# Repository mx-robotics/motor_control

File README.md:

moved to https://github.com/mx-car/motor_shield_teensy3.2

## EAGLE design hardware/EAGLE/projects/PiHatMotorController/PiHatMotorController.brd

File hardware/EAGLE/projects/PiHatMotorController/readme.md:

# Pin Maps for 2M Inverter Board and Teensy

## 1M Board

*  SPI: There are 2 AMS Rotary Encoders that send info, so there are 2 CS Pins.
	* CS1: 9
  * CS2: 15/A1
	* CLK: 13
	* MOSI: 11
	* MISO: 12
  
* Current Sense
	* IS_W: A17
	* IS_V: A16
	* IS_U: A15
  * IS_W1: A12
	* IS_V2: A13
	* IS_U2: A17
  
* INHIBIT Pins 
	* INH_W: 33
	* INH_V: 3
	* INH_U: 24
  * INH_W2: 0
	* INH_V2: 1
	* INH_U2: 2
  
* Servo Pins:
	* S_PWM1: 32
	* S_PWM2: 25
  
* IN Pins (for actively controlling the half-bridges with PWM)
	* They do not directly connect to Teensy and must be connected with cables. Candidate pins that use FTM0 are adjacent and are **21, 22 and 23**.
	* IN_W: 10
	* IN_V: 6
	* IN_U: 5
  * IN_W2: 23
	* IN_V2: 22
	* IN_U2: 21
  
* Hall Pins
	* HALL_W: A13
	* HALL_U: A12
	* HALL_V: A11
  * HALL_W: A13
	* HALL_U: A12
	* HALL_V: A11

* I2C Pins 0
	* SDA0: 18
	* SCL0: 19
* I2C Pins 1:
	* SDA1: 30
	* SCL1: 29

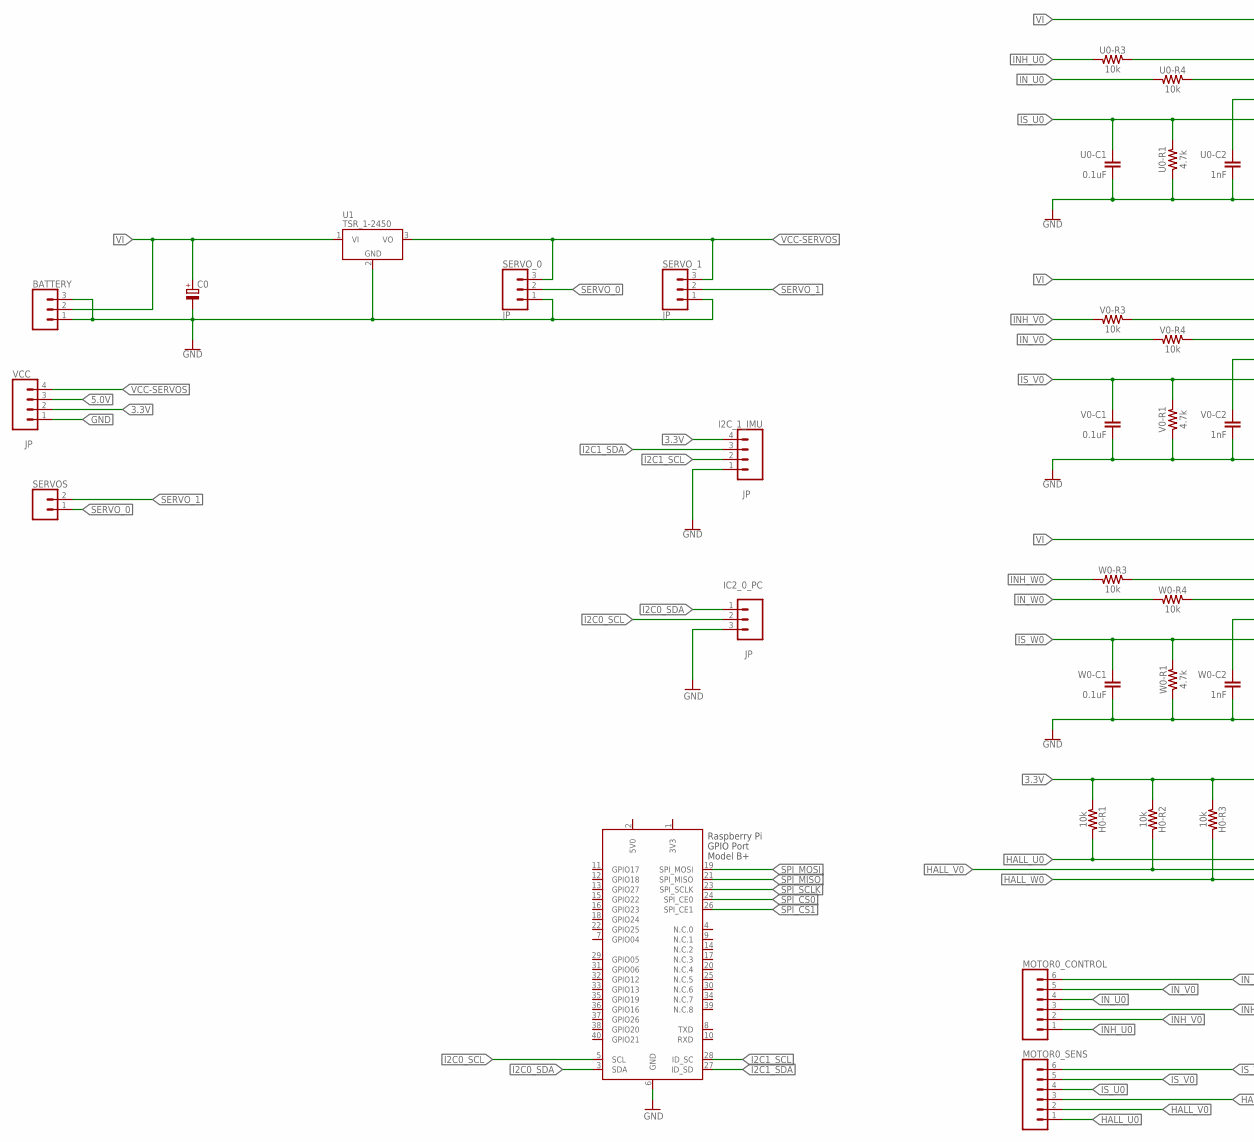
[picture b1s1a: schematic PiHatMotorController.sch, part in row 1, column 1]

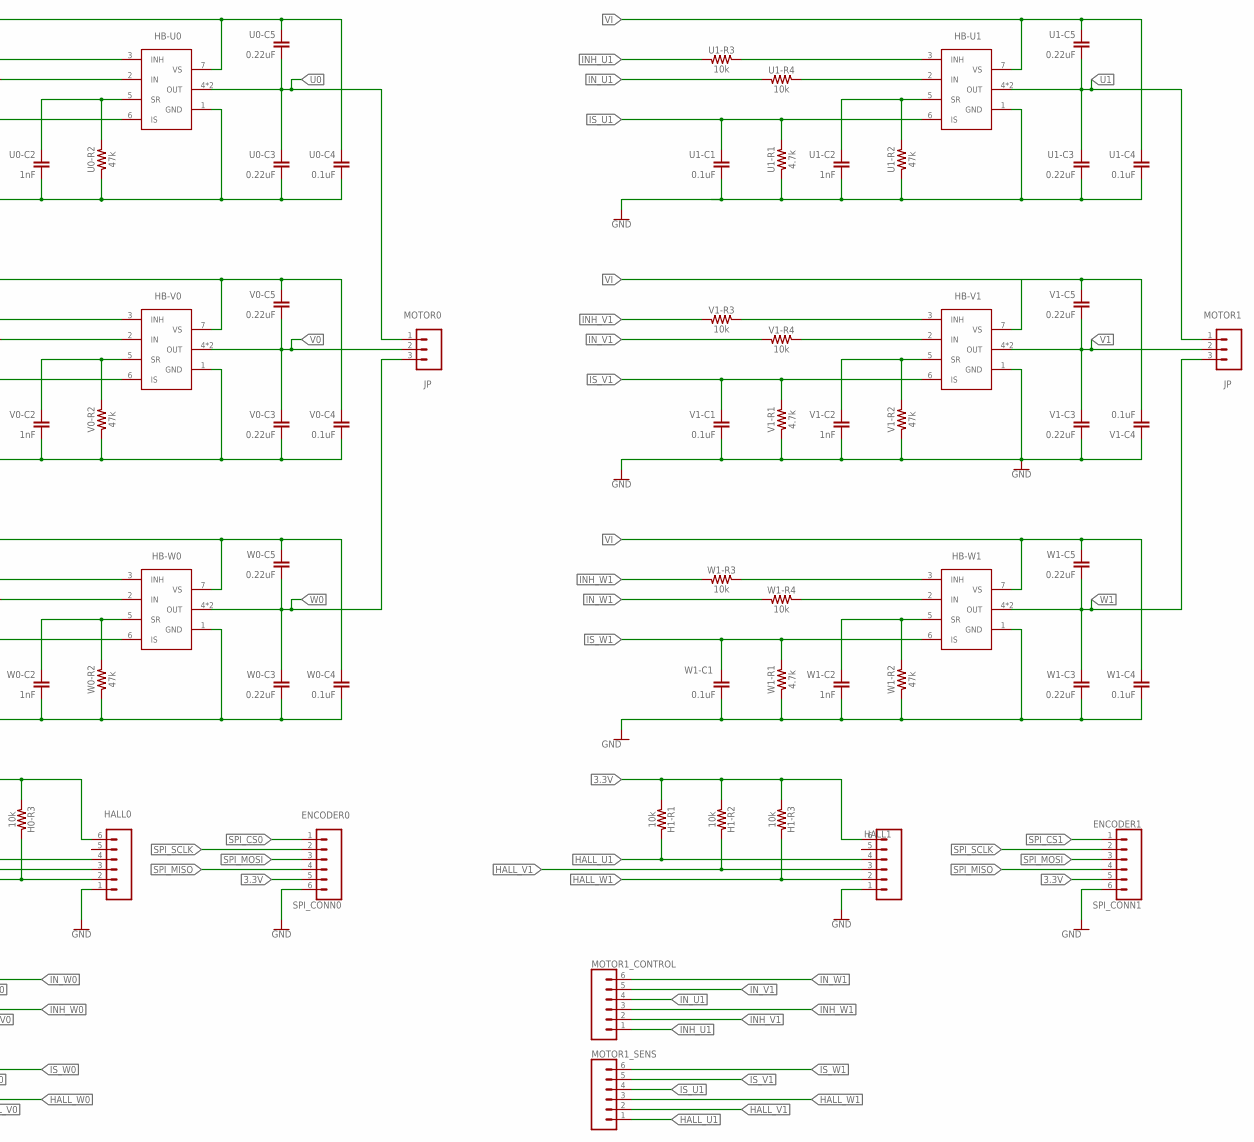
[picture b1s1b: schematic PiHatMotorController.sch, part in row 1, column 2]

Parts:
BATTERY: CONN_031X03_NO_SILK; 1X03_NO_SILK
C0: CPOL-EUE2,5-6E; E2,5-6E
H0-R1, H0-R2, H0-R3, H1-R1, H1-R2, H1-R3: 10k; 0603
HALL0, HALL1: CONN_06SMD-1MM; 1X06-1MM
HB-U0, HB-U1: IFX007TZZZZ; P-TO263-7-1
HB-V0, HB-V1: IFX007TZZZZ; P-TO263-7-1
HB-W0, HB-W1: IFX007TZZZZ; P-TO263-7-1
I2C_1_IMU: JP; 1X04_NO_SILK
IC2_0_PC: JP; 1X03_NO_SILK
MOTOR0, MOTOR1: JP; 1X03_NO_SILK
MOTOR0_CONTROL, MOTOR0_SENS, MOTOR1_CONTROL, MOTOR1_SENS: CONN_06NO_SILK_NO_POP; 1X06_NO_SILK
SERVOS: CONN_021X02_NO_SILK; 1X02_NO_SILK
SERVO_0, SERVO_1: JP; 1X03_NO_SILK
SPI_CONN0: ENCODER0; 1X06-1MM
SPI_CONN1: ENCODER1; 1X06-1MM
U0-C1, U0-C4, U1-C1, U1-C4: 0.1uF; 0603
U0-C2, U1-C2: 1nF; 0603
U0-C3, U0-C5, U1-C3, U1-C5: 0.22uF; 0603
U0-R1, U1-R1: 4.7k; 0603
U0-R2, U1-R2: 47k; 0603
U0-R3, U0-R4, U1-R3, U1-R4: 10k; 0603
U1: TSR_1-2450; TSR-1
V0-C1, V0-C4, V1-C1, V1-C4: 0.1uF; 0603
V0-C2, V1-C2: 1nF; 0603
V0-C3, V0-C5, V1-C3, V1-C5: 0.22uF; 0603
V0-R1, V1-R1: 4.7k; 0603
V0-R2, V1-R2: 47k; 0603
V0-R3, V0-R4, V1-R3, V1-R4: 10k; 0603
VCC: JP; 1X04_NO_SILK
W0-C1, W0-C4, W1-C1, W1-C4: 0.1uF; 0603
W0-C2, W1-C2: 1nF; 0603
W0-C3, W0-C5, W1-C3, W1-C5: 0.22uF; 0603
W0-R1, W1-R1: 4.7k; 0603
W0-R2, W1-R2: 47k; 0603
W0-R3, W0-R4, W1-R3, W1-R4: 10k; 0603
X1: RASPI_BOARD_B+_H; RASPI_BOARD_B+HAT

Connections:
3.3V: H0-R1.2, H0-R2.2, H0-R3.2, H1-R1.2, H1-R2.2, H1-R3.2, HALL0.6, HALL1.6, I2C_1_IMU.4, SPI_CONN0.5, SPI_CONN1.5, VCC.2
3V3: X1.1 (3V3)
5.0V: VCC.3
5V0: X1.2 (5V0)
GND: BATTERY.1, BATTERY.3, C0.-, HALL0.1, HALL1.1, HB-U0.1 (GND), HB-U1.1 (GND), HB-V0.1 (GND), HB-V1.1 (GND), HB-W0.1 (GND), HB-W1.1 (GND), I2C_1_IMU.1, IC2_0_PC.3, SERVO_0.1, SERVO_1.1, SPI_CONN0.6, SPI_CONN1.6, U0-C1.1, U0-C2.1, U0-C3.1, U0-C4.1, U0-R1.1, U0-R2.1, U1.2 (GND), U1-C1.1, U1-C2.1, U1-C3.1, U1-C4.1, U1-R1.1, U1-R2.1, V0-C1.1, V0-C2.1, V0-C3.1, V0-C4.1, V0-R1.1, V0-R2.1, V1-C1.1, V1-C2.1, V1-C3.1, V1-C4.1, V1-R1.1, V1-R2.1, VCC.1, W0-C1.1, W0-C2.1, W0-C3.1, W0-C4.1, W0-R1.1, W0-R2.1, W1-C1.1, W1-C2.1, W1-C3.1, W1-C4.1, W1-R1.1, W1-R2.1, X1.6 (GND)
HALL_U0: H0-R1.1, HALL0.4, MOTOR0_SENS.1
HALL_U1: H1-R1.1, HALL1.4, MOTOR1_SENS.1
HALL_V0: H0-R2.1, HALL0.3, MOTOR0_SENS.2
HALL_V1: H1-R2.1, HALL1.3, MOTOR1_SENS.2
HALL_W0: H0-R3.1, HALL0.2, MOTOR0_SENS.3
HALL_W1: H1-R3.1, HALL1.2, MOTOR1_SENS.3
HB_INH_U0: HB-U0.3 (INH), U0-R3.1
HB_INH_U1: HB-U1.3 (INH), U1-R3.1
HB_INH_V0: HB-V0.3 (INH), V0-R3.1
HB_INH_V1: HB-V1.3 (INH), V1-R3.1
HB_INH_W0: HB-W0.3 (INH), W0-R3.1
HB_INH_W1: HB-W1.3 (INH), W1-R3.1
HB_IN_U0: HB-U0.2 (IN), U0-R4.1
HB_IN_U1: HB-U1.2 (IN), U1-R4.1
HB_IN_V0: HB-V0.2 (IN), V0-R4.1
HB_IN_V1: HB-V1.2 (IN), V1-R4.1
HB_IN_W0: HB-W0.2 (IN), W0-R4.1
HB_IN_W1: HB-W1.2 (IN), W1-R4.1
I2C0_SCL: IC2_0_PC.2, X1.5 (SCL)
I2C0_SDA: IC2_0_PC.1, X1.3 (SDA)
I2C1_SCL: I2C_1_IMU.2, X1.28 (ID_SC)
I2C1_SDA: I2C_1_IMU.3, X1.27 (ID_SD)
INH_U0: MOTOR0_CONTROL.1, U0-R3.2
INH_U1: MOTOR1_CONTROL.1, U1-R3.2
INH_V0: MOTOR0_CONTROL.2, V0-R3.2
INH_V1: MOTOR1_CONTROL.2, V1-R3.2
INH_W0: MOTOR0_CONTROL.3, W0-R3.2
INH_W1: MOTOR1_CONTROL.3, W1-R3.2
IN_U0: MOTOR0_CONTROL.4, U0-R4.2
IN_U1: MOTOR1_CONTROL.4, U1-R4.2
IN_V0: MOTOR0_CONTROL.5, V0-R4.2
IN_V1: MOTOR1_CONTROL.5, V1-R4.2
IN_W0: MOTOR0_CONTROL.6, W0-R4.2
IN_W1: MOTOR1_CONTROL.6, W1-R4.2
IS_U0: HB-U0.6 (IS), MOTOR0_SENS.4, U0-C1.2, U0-R1.2
IS_U1: HB-U1.6 (IS), MOTOR1_SENS.4, U1-C1.2, U1-R1.2
IS_V0: HB-V0.6 (IS), MOTOR0_SENS.5, V0-C1.2, V0-R1.2
IS_V1: HB-V1.6 (IS), MOTOR1_SENS.5, V1-C1.2, V1-R1.2
IS_W0: HB-W0.6 (IS), MOTOR0_SENS.6, W0-C1.2, W0-R1.2
IS_W1: HB-W1.6 (IS), MOTOR1_SENS.6, W1-C1.2, W1-R1.2
SERVO_0: SERVOS.1, SERVO_0.2
SERVO_1: SERVOS.2, SERVO_1.2
SPI_CS0: SPI_CONN0.1, X1.24 (SPI_CE0)
SPI_CS1: SPI_CONN1.1, X1.26 (SPI_CE1)
SPI_MISO: SPI_CONN0.4, SPI_CONN1.4, X1.21 (SPI_MISO)
SPI_MOSI: SPI_CONN0.3, SPI_CONN1.3, X1.19 (SPI_MOSI)
SPI_SCLK: SPI_CONN0.2, SPI_CONN1.2, X1.23 (SPI_SCLK)
SR_U0: HB-U0.5 (SR), U0-C2.2, U0-R2.2
SR_U1: HB-U1.5 (SR), U1-C2.2, U1-R2.2
SR_V0: HB-V0.5 (SR), V0-C2.2, V0-R2.2
SR_V1: HB-V1.5 (SR), V1-C2.2, V1-R2.2
SR_W0: HB-W0.5 (SR), W0-C2.2, W0-R2.2
SR_W1: HB-W1.5 (SR), W1-C2.2, W1-R2.2
U0: HB-U0.4 (OUT), HB-U0.8 (OUT), MOTOR0.1, U0-C3.2, U0-C5.2
U1: HB-U1.4 (OUT), HB-U1.8 (OUT), MOTOR1.1, U1-C3.2, U1-C5.2
V0: HB-V0.4 (OUT), HB-V0.8 (OUT), MOTOR0.2, V0-C3.2, V0-C5.2
V1: HB-V1.4 (OUT), HB-V1.8 (OUT), MOTOR1.2, V1-C3.2, V1-C5.2
VCC-SERVOS: SERVO_0.3, SERVO_1.3, U1.3 (VO), VCC.4
VI: BATTERY.2, C0.+, HB-U0.7 (VS), HB-U1.7 (VS), HB-V0.7 (VS), HB-V1.7 (VS), HB-W0.7 (VS), HB-W1.7 (VS), U0-C4.2, U0-C5.1, U1.1 (VI), U1-C4.2, U1-C5.1, V0-C4.2, V0-C5.1, V1-C4.2, V1-C5.1, W0-C4.2, W0-C5.1, W1-C4.2, W1-C5.1
W0: HB-W0.4 (OUT), HB-W0.8 (OUT), MOTOR0.3, W0-C3.2, W0-C5.2
W1: HB-W1.4 (OUT), HB-W1.8 (OUT), MOTOR1.3, W1-C3.2, W1-C5.2

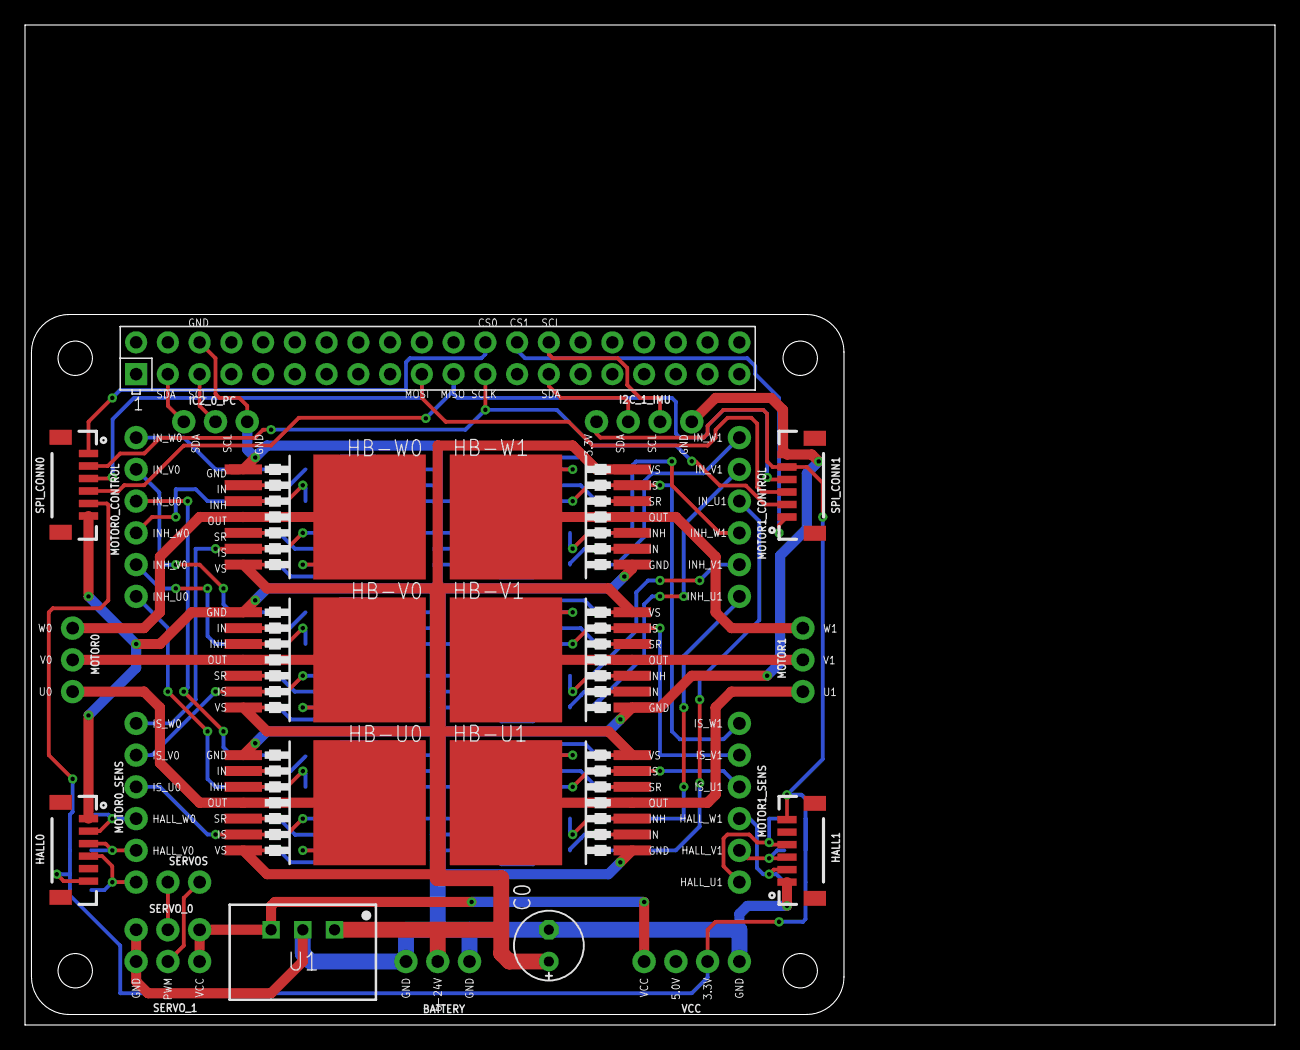
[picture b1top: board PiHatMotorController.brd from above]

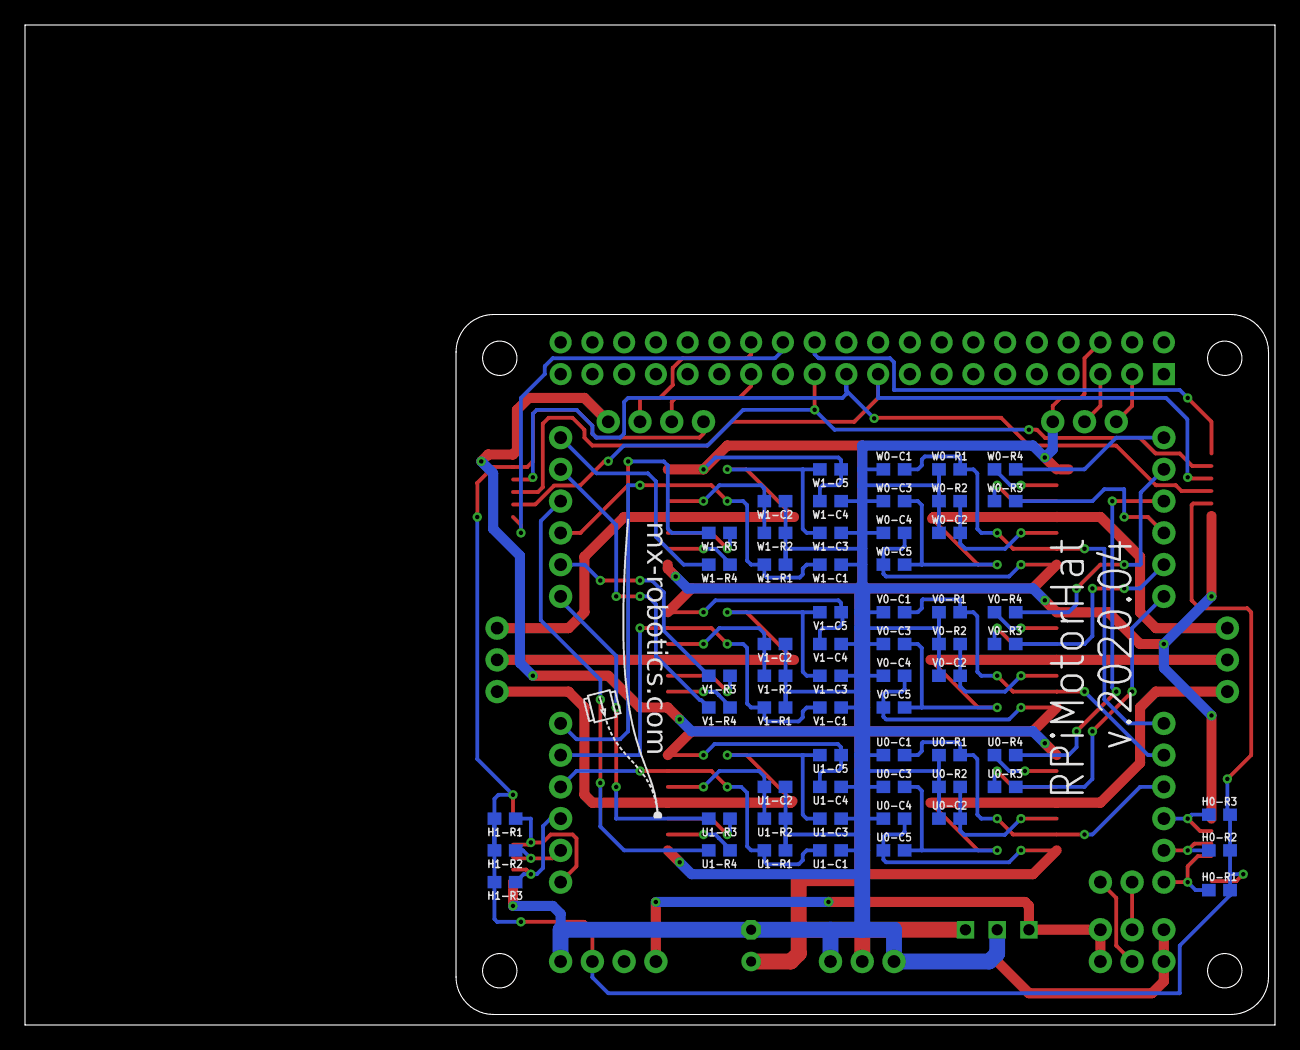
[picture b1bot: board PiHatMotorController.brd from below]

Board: 2 copper layers, 100.0 x 80.0 mm, 86 parts (60 on the bottom side), 63 nets.

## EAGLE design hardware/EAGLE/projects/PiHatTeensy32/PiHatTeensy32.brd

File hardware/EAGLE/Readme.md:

# Eagle Project for MotorShields
## Setup
Set all Directories as shown in the image or make a soft link on the eagle folder  to 
´´´
ln -s $HOME/projects/rcar/motor_control/hardware/EAGLE $HOME/
´´´

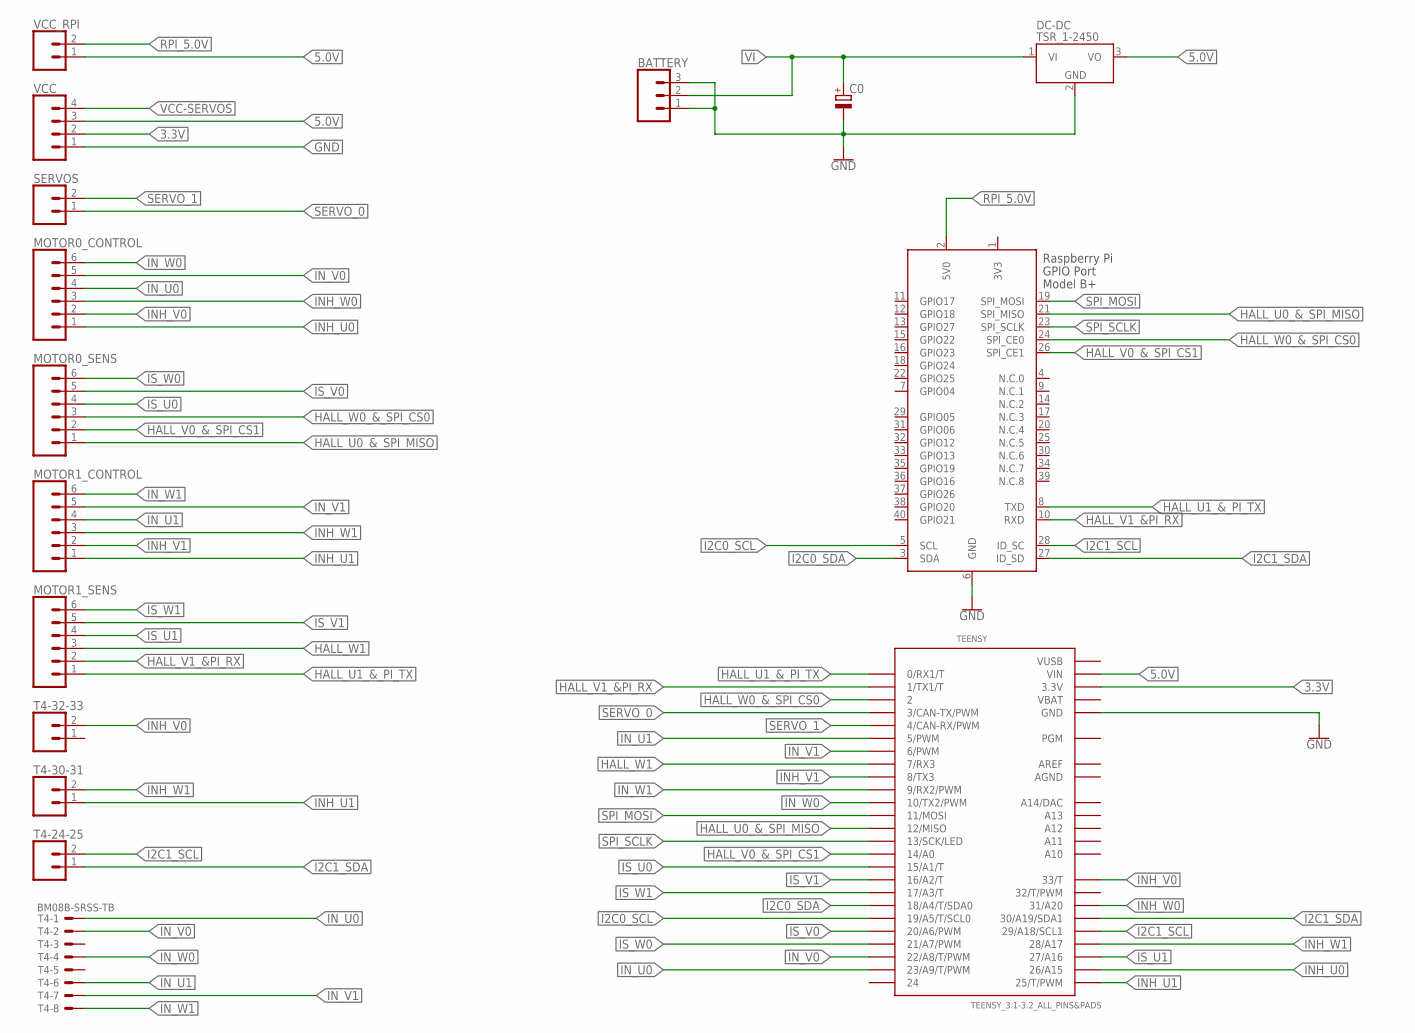
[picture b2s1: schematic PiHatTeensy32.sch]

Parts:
BATTERY: CONN_031X03_NO_SILK; 1X03_NO_SILK
C0: CPOL-EUE2,5-6E; E2,5-6E
DC-DC: TSR_1-2450; TSR-1
MOTOR0_CONTROL, MOTOR0_SENS, MOTOR1_CONTROL, MOTOR1_SENS: CONN_06NO_SILK_NO_POP; 1X06_NO_SILK
SERVOS: CONN_021X02_NO_SILK; 1X02_NO_SILK
T4: BM08B-SRSS-TB
T4-24-25, T4-30-31, T4-32-33: CONN_021X02_NO_SILK; 1X02_NO_SILK
TEENSY: TEENSY_3.1-3.2_ALL_PINS&PADS; TEENSY_3.0-3.2_ALL_PINS_&_PADS
VCC: CONN_041X04_NO_SILK; 1X04_NO_SILK
VCC_RPI: CONN_021X02_NO_SILK; 1X02_NO_SILK
X1: RASPI_BOARD_B+_H; RASPI_BOARD_B+HAT

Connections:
3.3V: TEENSY.3.3V, TEENSY.3.3V1 (3.3V), TEENSY.3.3V2 (3.3V), VCC.2
3V3: X1.1 (3V3)
5.0V: DC-DC.3 (VO), TEENSY.VIN, VCC.3, VCC_RPI.1
AGND: TEENSY.AGND
AREF: TEENSY.AREF
GND: BATTERY.1, BATTERY.3, C0.-, DC-DC.2 (GND), TEENSY.GND, TEENSY.GND1 (GND), TEENSY.GND2 (GND), VCC.1, X1.6 (GND)
HALL_U0_&_SPI_MISO: MOTOR0_SENS.1, TEENSY.12 (12/MISO), X1.21 (SPI_MISO)
HALL_U1_&_PI_TX: MOTOR1_SENS.1, TEENSY.0 (0/RX1/T), X1.8 (TXD)
HALL_V0_&_SPI_CS1: MOTOR0_SENS.2, TEENSY.14/A0, X1.26 (SPI_CE1)
HALL_V1_&PI_RX: MOTOR1_SENS.2, TEENSY.1 (1/TX1/T), X1.10 (RXD)
HALL_W0_&_SPI_CS0: MOTOR0_SENS.3, TEENSY.2, X1.24 (SPI_CE0)
HALL_W1: MOTOR1_SENS.3, TEENSY.7 (7/RX3)
I2C0_SCL: TEENSY.19/A5 (19/A5/T/SCL0), X1.5 (SCL)
I2C0_SDA: TEENSY.18/A4 (18/A4/T/SDA0), X1.3 (SDA)
I2C1_SCL: T4-24-25.2, TEENSY.29 (29/A18/SCL1), X1.28 (ID_SC)
I2C1_SDA: T4-24-25.1, TEENSY.30 (30/A19/SDA1), X1.27 (ID_SD)
INH_U0: MOTOR0_CONTROL.1, TEENSY.26 (26/A15)
INH_U1: MOTOR1_CONTROL.1, T4-30-31.1, TEENSY.25 (25/T/PWM)
INH_V0: MOTOR0_CONTROL.2, T4-32-33.2, TEENSY.33 (33/T)
INH_V1: MOTOR1_CONTROL.2, TEENSY.8 (8/TX3)
INH_W0: MOTOR0_CONTROL.3, TEENSY.31 (31/A20)
INH_W1: MOTOR1_CONTROL.3, T4-30-31.2, TEENSY.28 (28/A17)
IN_U0: MOTOR0_CONTROL.4, T4.1, TEENSY.23/A9 (23/A9/T/PWM)
IN_U1: MOTOR1_CONTROL.4, T4.6, TEENSY.5 (5/PWM)
IN_V0: MOTOR0_CONTROL.5, T4.2, TEENSY.22/A8 (22/A8/T/PWM)
IN_V1: MOTOR1_CONTROL.5, T4.7, TEENSY.6 (6/PWM)
IN_W0: MOTOR0_CONTROL.6, T4.4, TEENSY.10 (10/TX2/PWM)
IN_W1: MOTOR1_CONTROL.6, T4.8, TEENSY.9 (9/RX2/PWM)
IS_U0: MOTOR0_SENS.4, TEENSY.15/A1 (15/A1/T)
IS_U1: MOTOR1_SENS.4, TEENSY.27 (27/A16)
IS_V0: MOTOR0_SENS.5, TEENSY.20/A6 (20/A6/PWM)
IS_V1: MOTOR1_SENS.5, TEENSY.16/A2 (16/A2/T)
IS_W0: MOTOR0_SENS.6, TEENSY.21/A7 (21/A7/PWM)
IS_W1: MOTOR1_SENS.6, TEENSY.17/A3 (17/A3/T)
RPI_5.0V: VCC_RPI.2, X1.2 (5V0)
SERVO_0: SERVOS.1, TEENSY.3 (3/CAN-TX/PWM)
SERVO_1: SERVOS.2, TEENSY.4 (4/CAN-RX/PWM)
SPI_MOSI: TEENSY.11 (11/MOSI), X1.19 (SPI_MOSI)
SPI_SCLK: TEENSY.13 (13/SCK/LED), X1.23 (SPI_SCLK)
VBAT: TEENSY.VBAT
VCC-SERVOS: VCC.4
VI: BATTERY.2, C0.+, DC-DC.1 (VI)
VUSB: TEENSY.VUSB

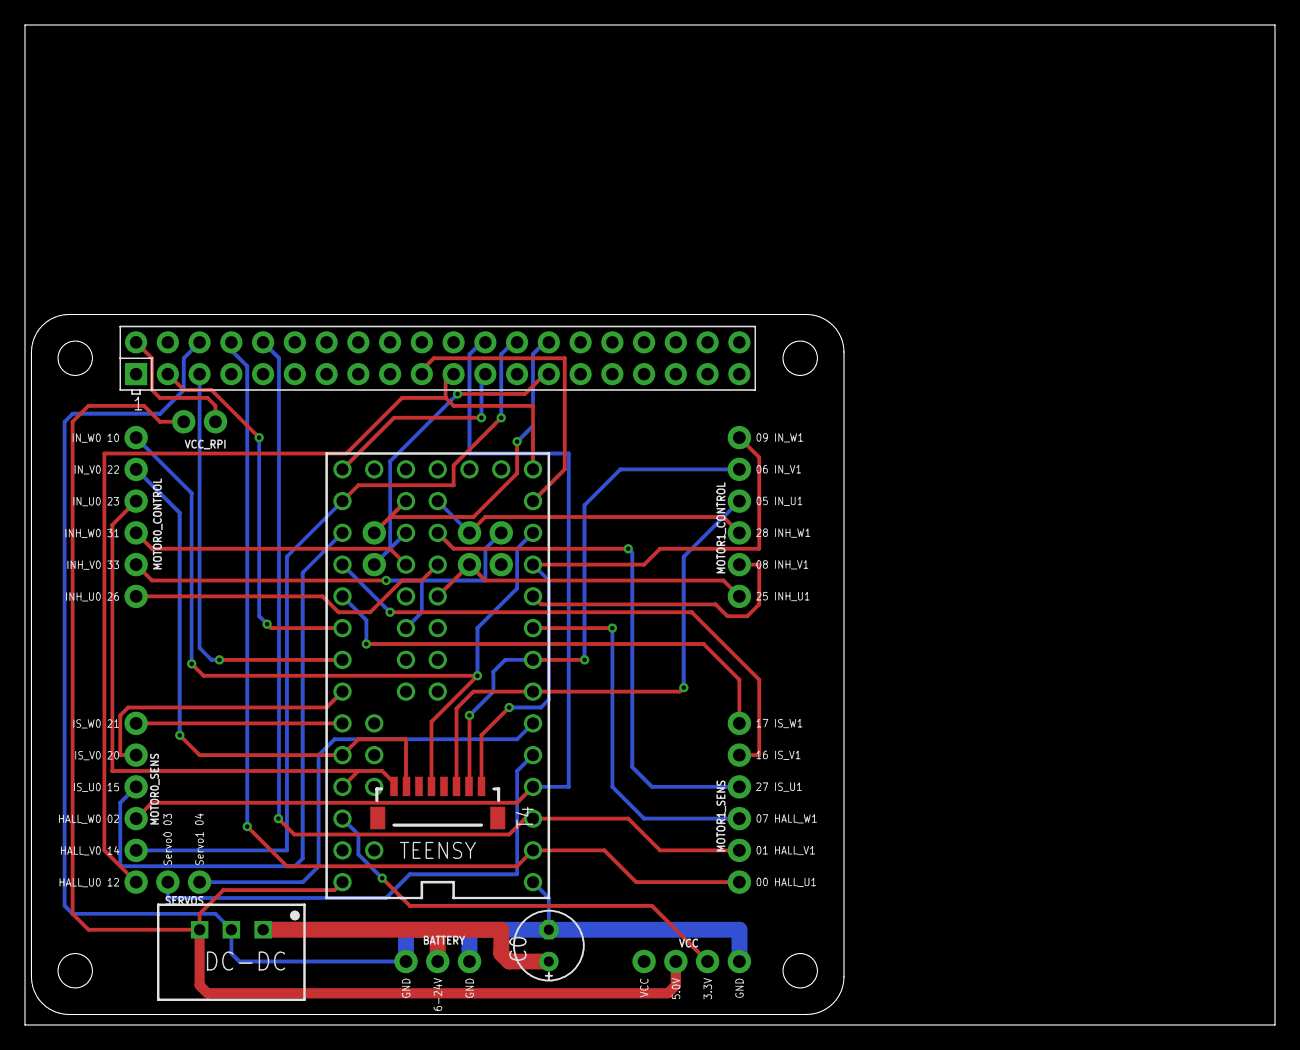
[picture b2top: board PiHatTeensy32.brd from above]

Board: 2 copper layers, 100.0 x 80.0 mm, 16 parts (0 on the bottom side), 37 nets.

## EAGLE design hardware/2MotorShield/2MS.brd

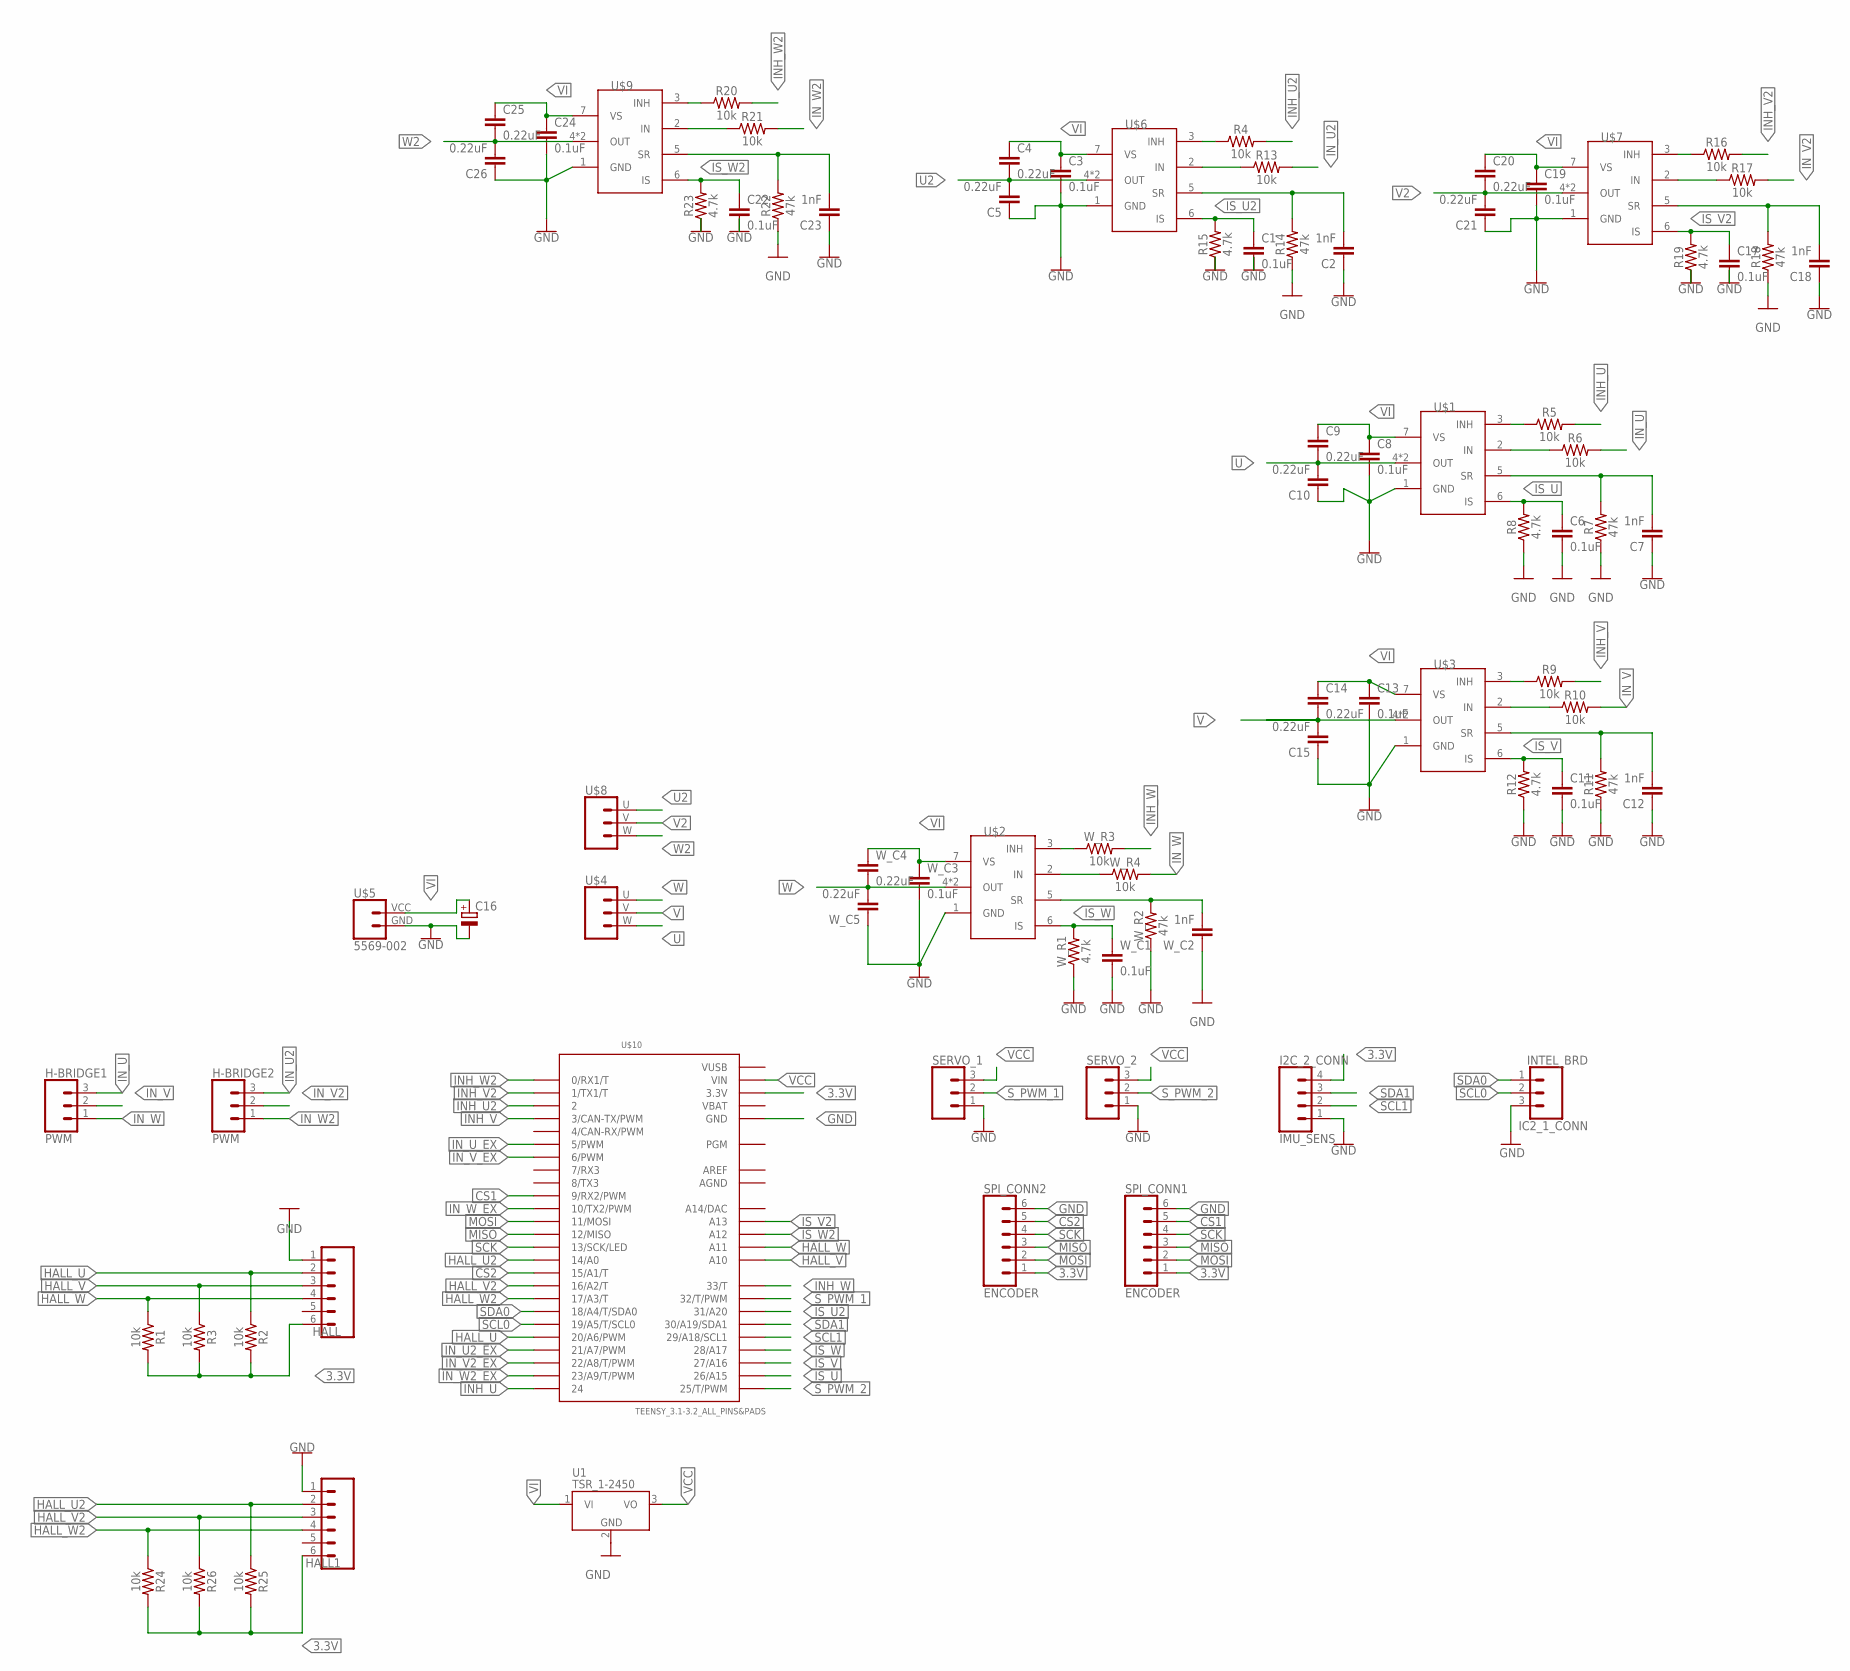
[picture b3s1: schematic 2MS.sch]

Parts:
C1, C3, C6, C8, C11, C13, C17, C19, C22, C24: 0.1uF; 0603
C2, C7, C12, C18, C23: 1nF; 0603
C4, C5, C9, C10, C14, C15, C20, C21, C25, C26: 0.22uF; 0603
C16: CPOL-EUE2,5-6E; E2,5-6E
H-BRIDGE1, H-BRIDGE2: PWM; 1X03_NO_SILK
HALL, HALL1: CONN_06SMD-1MM; 1X06-1MM
I2C_2_CONN: IMU_SENS; 1X04_NO_SILK
IC2_1_CONN: INTEL_BRD; 1X03_NO_SILK
R1, R2, R3, R4, R5, R6, R9, R10, R13, R16, R17, R20, R21, R24, R25, R26: 10k; 0603
R7, R11, R14, R18, R22: 47k; 0603
R8, R12, R15, R19, R23: 4.7k; 0603
SERVO_1, SERVO_2: CONN_031X03_NO_SILK; 1X03_NO_SILK
SPI_CONN1, SPI_CONN2: ENCODER; 1X06-1MM
U1: TSR_1-2450; TSR-1
U$1, U$2, U$3, U$6, U$7, U$9: IFX007TZZZZ; P-TO263-7-1
U$4, U$8: 5569-003
U$5: 5569-002
U$10: TEENSY_3.1-3.2_ALL_PINS&PADS; TEENSY_3.0-3.2_ALL_PINS_&_PADS
W_C1, W_C3: 0.1uF; 0603
W_C2: 1nF; 0603
W_C4, W_C5: 0.22uF; 0603
W_R1: 4.7k; 0603
W_R2: 47k; 0603
W_R3, W_R4: 10k; 0603

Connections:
3.3V: HALL.6, HALL1.6, I2C_2_CONN.4, R1.2, R2.2, R3.2, R24.2, R25.2, R26.2, SPI_CONN1.1, SPI_CONN2.1, U$10.3.3V, U$10.3.3V1 (3.3V), U$10.3.3V2 (3.3V)
AGND: U$10.AGND
AREF: U$10.AREF
CS1: SPI_CONN1.5, U$10.9 (9/RX2/PWM)
CS2: SPI_CONN2.5, U$10.15/A1 (15/A1/T)
GND: C1.2, C2.1, C3.2, C5.1, C6.2, C7.1, C8.2, C10.1, C11.2, C12.1, C13.2, C15.1, C16.-, C17.2, C18.1, C19.2, C21.1, C22.2, C23.1, C24.2, C26.1, HALL.1, HALL1.1, I2C_2_CONN.1, IC2_1_CONN.3, R7.1, R8.1, R11.1, R12.1, R14.1, R15.1, R18.1, R19.1, R22.1, R23.1, SERVO_1.1, SERVO_2.1, SPI_CONN1.6, SPI_CONN2.6, U1.2 (GND), U$1.1 (GND), U$2.1 (GND), U$3.1 (GND), U$5.GND (1), U$6.1 (GND), U$7.1 (GND), U$9.1 (GND), U$10.GND, U$10.GND1 (GND), U$10.GND2 (GND), W_C1.2, W_C2.1, W_C3.2, W_C5.1, W_R1.1, W_R2.1
HALL_U: HALL.2, R2.1, U$10.20/A6 (20/A6/PWM)
HALL_U2: HALL1.2, R25.1, U$10.14/A0
HALL_V: HALL.3, R3.1, U$10.A10
HALL_V2: HALL1.3, R26.1, U$10.16/A2 (16/A2/T)
HALL_W: HALL.4, R1.1, U$10.A11
HALL_W2: HALL1.4, R24.1, U$10.17/A3 (17/A3/T)
INH_U: R5.2, U$10.24
INH_U2: R4.2, U$10.2
INH_V: R9.2, U$10.3 (3/CAN-TX/PWM)
INH_V2: R16.2, U$10.1 (1/TX1/T)
INH_W: U$10.33 (33/T), W_R3.2
INH_W2: R20.2, U$10.0 (0/RX1/T)
IN_U: H-BRIDGE1.3, R6.2
IN_U2: H-BRIDGE2.3, R13.2
IN_U2_EX: U$10.21/A7 (21/A7/PWM)
IN_U_EX: U$10.5 (5/PWM)
IN_V: H-BRIDGE1.2, R10.2
IN_V2: H-BRIDGE2.2, R17.2
IN_V2_EX: U$10.22/A8 (22/A8/T/PWM)
IN_V_EX: U$10.6 (6/PWM)
IN_W: H-BRIDGE1.1, W_R4.2
IN_W2: H-BRIDGE2.1, R21.2
IN_W2_EX: U$10.23/A9 (23/A9/T/PWM)
IN_W_EX: U$10.10 (10/TX2/PWM)
IS_U: C6.1, R8.2, U$1.6 (IS), U$10.26 (26/A15)
IS_U2: C1.1, R15.2, U$6.6 (IS), U$10.31 (31/A20)
IS_V: C11.1, R12.2, U$3.6 (IS), U$10.27 (27/A16)
IS_V2: C17.1, R19.2, U$7.6 (IS), U$10.A13
IS_W: U$2.6 (IS), U$10.28 (28/A17), W_C1.1, W_R1.2
IS_W2: C22.1, R23.2, U$9.6 (IS), U$10.A12
MISO: SPI_CONN1.3, SPI_CONN2.3, U$10.12 (12/MISO)
MOSI: SPI_CONN1.2, SPI_CONN2.2, U$10.11 (11/MOSI)
unnamed: U$2.3 (INH), W_R3.1
unnamed: C12.2, R11.2, U$3.5 (SR)
unnamed: U$2.5 (SR), W_C2.2, W_R2.2
unnamed: C7.2, R7.2, U$1.5 (SR)
unnamed: R5.1, U$1.3 (INH)
unnamed: R6.1, U$1.2 (IN)
unnamed: R4.1, U$6.3 (INH)
unnamed: R9.1, U$3.3 (INH)
unnamed: R13.1, U$6.2 (IN)
unnamed: U$2.2 (IN), W_R4.1
unnamed: C2.2, R14.2, U$6.5 (SR)
unnamed: R10.1, U$3.2 (IN)
unnamed: R16.1, U$7.3 (INH)
unnamed: R17.1, U$7.2 (IN)
unnamed: C18.2, R18.2, U$7.5 (SR)
unnamed: R20.1, U$9.3 (INH)
unnamed: R21.1, U$9.2 (IN)
unnamed: C23.2, R22.2, U$9.5 (SR)
SCK: SPI_CONN1.4, SPI_CONN2.4, U$10.13 (13/SCK/LED)
SCL0: IC2_1_CONN.2, U$10.19/A5 (19/A5/T/SCL0)
SCL1: I2C_2_CONN.2, U$10.29 (29/A18/SCL1)
SDA0: IC2_1_CONN.1, U$10.18/A4 (18/A4/T/SDA0)
SDA1: I2C_2_CONN.3, U$10.30 (30/A19/SDA1)
S_PWM_1: SERVO_1.2, U$10.32 (32/T/PWM)
S_PWM_2: SERVO_2.2, U$10.25 (25/T/PWM)
U: C9.2, C10.2, U$1.4 (OUT), U$1.8 (OUT), U$4.W (V)
U2: C4.2, C5.2, U$6.4 (OUT), U$6.8 (OUT), U$8.U (W)
V: C14.2, C15.2, U$3.4 (OUT), U$3.8 (OUT), U$4.V (U)
V2: C20.2, C21.2, U$7.4 (OUT), U$7.8 (OUT), U$8.V (U)
VBAT: U$10.VBAT
VCC: SERVO_1.3, SERVO_2.3, U1.3 (VO), U$10.VIN
VI: C3.1, C4.1, C8.1, C9.1, C13.1, C14.1, C16.+, C19.1, C20.1, C24.1, C25.1, U1.1 (VI), U$1.7 (VS), U$2.7 (VS), U$3.7 (VS), U$5.VCC (2), U$6.7 (VS), U$7.7 (VS), U$9.7 (VS), W_C3.1, W_C4.1
VUSB: U$10.VUSB
W: U$2.4 (OUT), U$2.8 (OUT), U$4.U (W), W_C4.2, W_C5.2
W2: C25.2, C26.2, U$8.W (V), U$9.4 (OUT), U$9.8 (OUT)

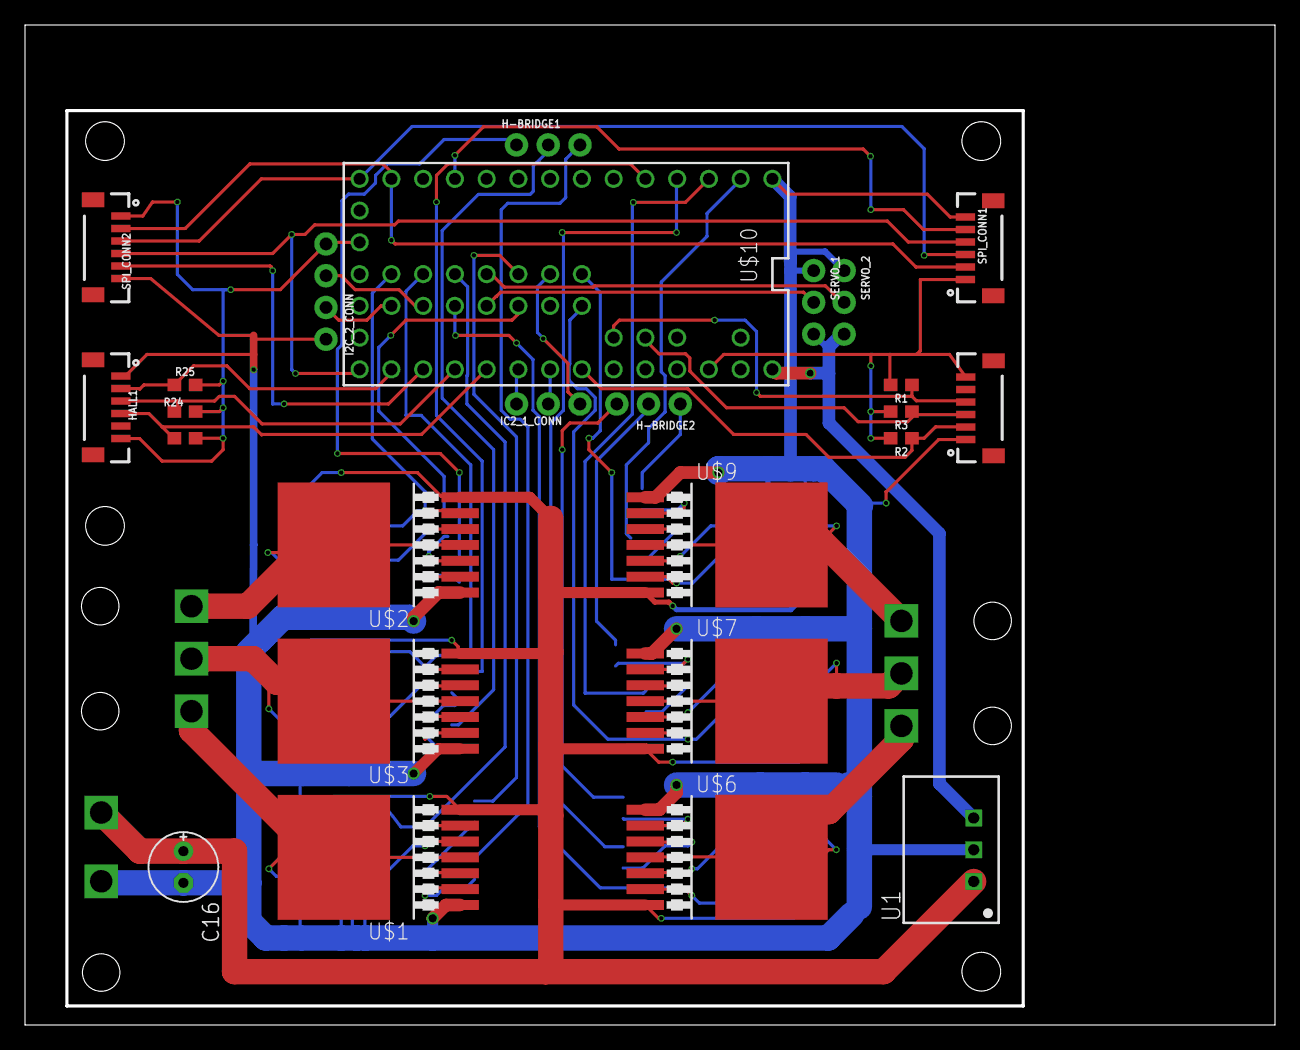
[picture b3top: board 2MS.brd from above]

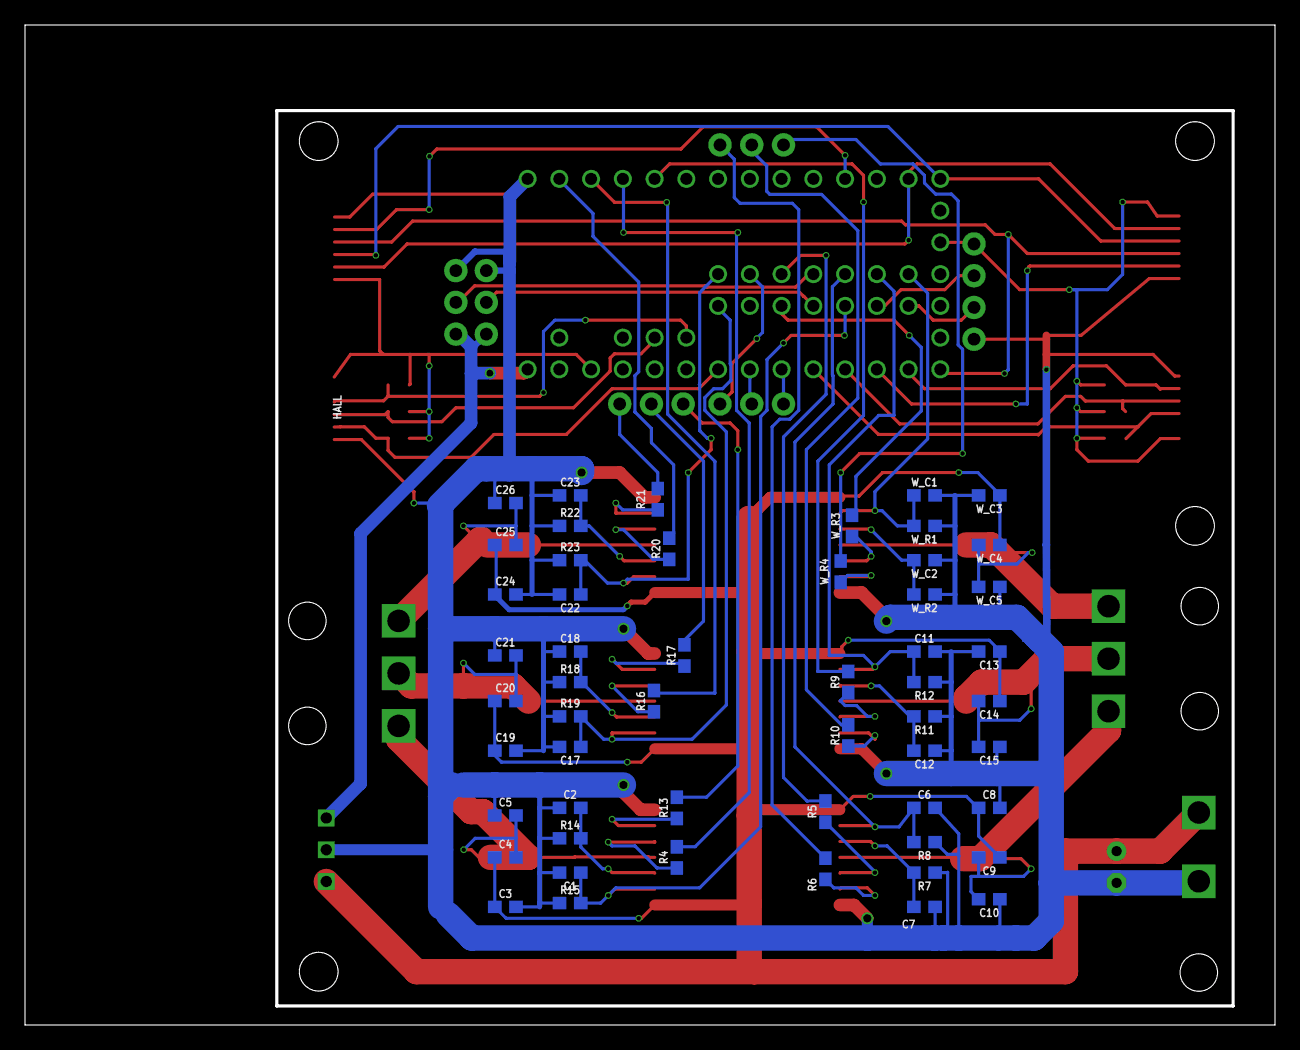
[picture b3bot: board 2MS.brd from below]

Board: 2 copper layers, 100.0 x 80.0 mm, 82 parts (55 on the bottom side), 63 nets.

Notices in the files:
parts and their libraries:
SparkFun-Capacitors: Licensing: Creative Commons ShareAlike 4.0 International - https://creativecommons.org/licenses/by-sa/4.0
